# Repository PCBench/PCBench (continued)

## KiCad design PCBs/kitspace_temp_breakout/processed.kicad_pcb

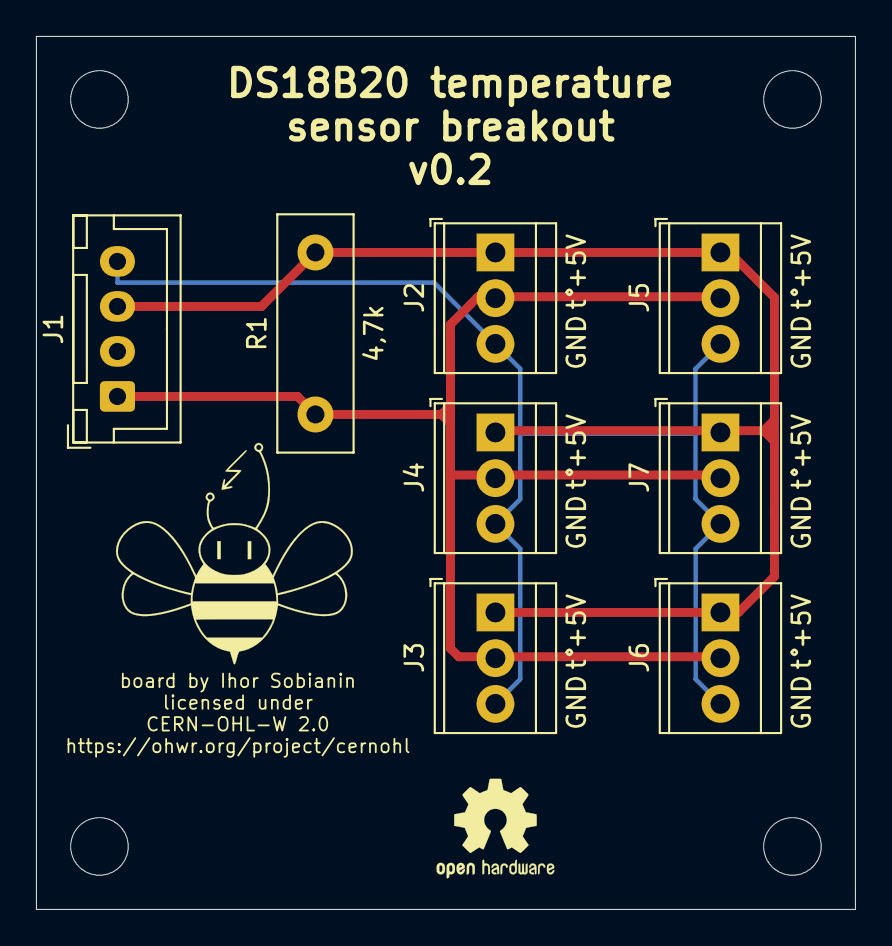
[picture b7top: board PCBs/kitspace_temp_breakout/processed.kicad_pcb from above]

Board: 2 copper layers, 45.5 x 48.5 mm, 8 parts (0 on the bottom side), 3 nets.

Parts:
J1: Conn_01x04; JST_XH_B4B-XH-A_1x04_P2.50mm_Vertical
J2, J3, J4, J5, J6, J7: Conn_01x03; TerminalBlock_TE_282834-3_1x03_P2.54mm_Horizontal
R1: 4,7k; R_Box_L13.0mm_W4.0mm_P9.00mm

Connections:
+5V: J1.3, J2.1, J3.1, J4.1, J5.1, J6.1, J7.1, R1.2
GND: J1.4, J2.3, J3.3, J4.3, J5.3, J6.3, J7.3
esp_pin: J1.1, J2.2, J3.2, J4.2, J5.2, J6.2, J7.2, R1.1
